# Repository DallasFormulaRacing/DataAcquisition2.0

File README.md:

> This repository was archived on Jan 10, 2025.

# `DataAcquisition2.0`

---
## Deprecation Notice 🚨
This repository has been deprecated. It is no longer actively maintained or updated. For the current and active IC Embedded project, please refer to the Wheel Base Sensor System [ repository](https://github.com/DallasFormulaRacing/WheelBaseSensorSystem).

---
🏁 For documentation, checkout our [Wiki](https://github.com/DallasFormulaRacing/DataAcquisition2.0/wiki)!

- Firmware libraries are maintained in the [DAQ Firmware Libraries](https://github.com/DallasFormulaRacing/DAQ-Firmware-Libraries) repo.
- Custom PCB revisions are maintained in the [DAQ-PCB](https://github.com/DallasFormulaRacing/DAQ-PCB) repo.
- When you clone this library, make sure that you add the --recurse-submodules flag
  
## Table of Contents
1. [Objective](#objective)
2. [User Features](#user-features)
3. [Hardware and Equipment](#hardware-and-equipment)
4. [Firmware Tech Stack](#firmware-tech-stack)
5. [Automation](#automation)
6. [Future Plans](#future-plans)
7. [Deprecated Technologies](#deprecated-technologies)

## Objective:
- A Data Acquisition (DAQ) System for interfacing with the vehicle ECU and additional sensors.
- Build the first fully-fledged DAQ with re-usable code through:
    - The Layered Architecture design pattern
    - Modularity of components
    - Hardware abstraction
- Efficiently record data to a CSV file for system testing & refinement of other vehicle components via analyses.
- Make sensor data conveniently accessible for the whole DFR organization.
- To be used in tandem with DFR's [DataAnalyzer](https://github.com/DallasFormulaRacing/DataAnalyzer).

## User Features
| Supported Logging Method | Library Completion    |
| :----------------------- | :--------------------:|
| Micro-SD Card            |                       |
| USB Flash Drive          | <span>&#10004;</span> |
| Wireless Transmission    |                       |

## Hardware and Equipment
### Target Device
The [STM32 Nucleo F429ZI](https://www.st.com/en/evaluation-tools/nucleo-f429zi.html) microcontroller development board is used as the current target device for code merged to the `main` and `develop` branches. Theoretically, other Arm Cortex M4 based STM32 devices with the necessary peripherals should be able to run the same program.

### Input
| Component Type        | Supported Hardware Device                                                                                            | Library Completion    |
| :-------------------- |:-------------------------------------------------------------------------------------------------------------------- | :--------------------:|
| Linear Potentiometer  | - [SLS 1322-3](https://www.activesensors.com/products/linear-position-sensors/general-purpose-linear-potentiometers) | <span>&#10004;</span> |
| Accelerometer         | - [LSM303DLHC](https://www.adafruit.com/product/1714)                                                                | <span>&#10004;</span> |
| Gyroscope             | - [L3GD20H](https://www.adafruit.com/product/1714)                                                                   | <span>&#10004;</span> |
| Magnetometer          | - [L3GD20H](https://www.adafruit.com/product/1714)                                                                   | <span>&#10004;</span> |
| GPS/GNSS              | - [NEO-M9N](https://www.sparkfun.com/products/15733)                                                                 |                       |
| Strain Gauges         |                                                                                                                      |                       |
| Tire Temperature      | - [MLX90614](https://www.sparkfun.com/products/9570)                                                                 |                       |
| ECU                   | - [PE3-8400P](https://pe-ltd.com/product/pe3-8400p/)                                                                 | <span>&#10004;</span> |

For additional information regarding each device and its implemention, refer to our [Wiki](https://github.com/DallasFormulaRacing/DataAcquisition2.0/wiki).

### Output
A CSV file with associate a timestamp with the following sampled data.

| Computed Output                | Supported Units                                         |
| :----------------------------- |:------------------------------------------------------- |
| Suspension Travel Displacement | - Inches <br /> - Millimeters                           |
| Acceleration (3 DoF)           | - m/s^2 <br /> - Gs                                     |
| Rotational Velocity (3 DoF)    | - Degrees per second <br /> - Radians per second        |
| Location Coordinates           | - Altitude <br /> - Latitude <br /> - Longitude         |
| External Force                 | - Stress <br /> - Torque <br /> - Pressure              |
| Tire Temperature               | - Farenheit <br /> - Celsius                            |
| Motor Shaft Speed              | - Revolutions per Minute (RPM)                          |
| Throttle Position              | - Percentage                                            |
| Fuel Open Time                 | - Milliseconds                                          |
| Ignition Angle                 | - Degrees                                               |
| Atmospheric Pressure           | - Pound per Square Inch (PSI) <br /> - Kilopascal (kPa) |
| Intake Manifold Pressure       | - Pound per Square Inch (PSI) <br /> - Kilopascal (kPa) |
| Exhaust Oxygen                 | - Lambda                                                |

## Firmware Tech Stack
- STM32 Hardware Abstraction Layer ([HAL](https://www.st.com/resource/en/user_manual/um1725-description-of-stm32f4-hal-and-lowlayer-drivers-stmicroelectronics.pdf))
  - Generated by STM32CubeMX within the CubeIDE environment, which also provides the `arm-none-eabi` toolchain.
  - Serves as a set of drivers or a Board Support Package (BSP) to interface with the microcontroller.
- [FreeRTOS](https://www.freertos.org/index.html)
  - Multi-threading and concurrent programming.
  - For optimizing timing and performance.
- [CMSIS-RTOS v2](https://www.keil.com/pack/doc/CMSIS/RTOS2/html/group__CMSIS__RTOS.html)
  - Not to be mistaken for another RTOS framework.
  - An abstraction layer for interacting with an RTOS framework (i.e., FreeRTOS).
- [FatFS](http://elm-chan.org/fsw/ff/)
  - For maintaining the FAT file system.
  - Allows users to access the resulting CSV file on any device

## Automation
- Unit tests are developed using [Google Test](https://google.github.io/googletest/) and are maintained in `DAQ_System/Tests`.
- See our [Unit Testing page](https://github.com/DallasFormulaRacing/DataAcquisition2.0/wiki/Unit-Testing) for running them locally by leveraging [Docker](https://docs.docker.com/get-started/overview/).
- Continuous Integration (CI)
  - The firmware is compiled as an stm32CubeIDE project using the following GitHub Action: [xanderhendriks/action-build-stm32cubeide](https://github.com/marketplace/actions/build-stm32cubeide-project).
  - The unit tests are compiled and ran using [CMake](https://cmake.org/cmake/help/latest/index.html) with [Ninja](https://ninja-build.org/manual.html). 

## Future Plans
- Developing for a dual-core STM32H7 microcontroller.
  - The Cortex M4 core may focus on sampling data from sensors.
  - The Cortex M7 core may focus on outputting the processed data.
  - Both cores may run FreeRTOS for organizational purposes.
  - Both cores may communicate and synchronize with each other using the OpenAMP framework.

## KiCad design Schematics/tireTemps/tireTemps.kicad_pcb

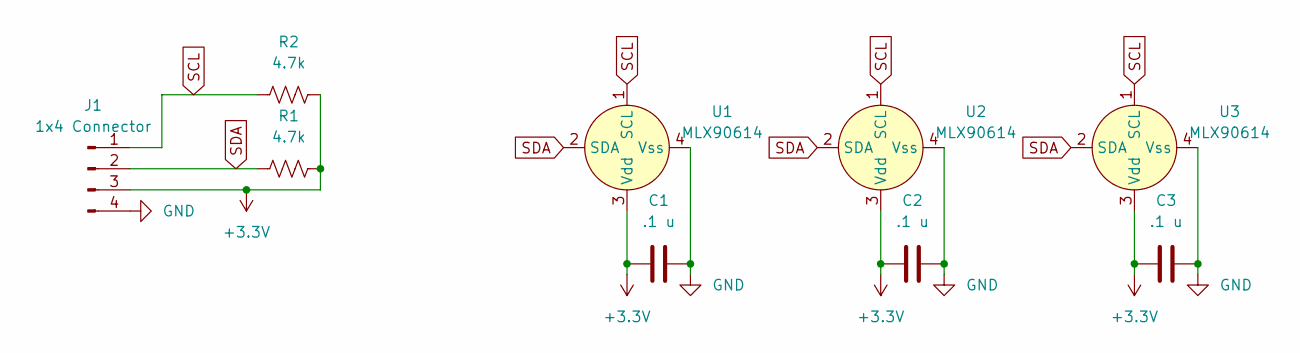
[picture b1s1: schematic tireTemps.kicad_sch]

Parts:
C1, C2, C3: .1 u; C_0603_1608Metric
J1: 1x4 Connector; Molex_KK-254_AE-6410-04A_1x04_P2.54mm_Vertical
R1, R2: 4.7k; R_0603_1608Metric
U1, U2, U3: MLX90614; TO-39-4

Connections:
+3.3V: C1.1, C2.1, C3.1, J1.3, R1.2, R2.2, U1.3 (Vdd), U2.3 (Vdd), U3.3 (Vdd)
GND: C1.2, C2.2, C3.2, J1.4, U1.4 (Vss), U2.4 (Vss), U3.4 (Vss)
SCL: J1.1, R2.1, U1.1 (SCL), U2.1 (SCL), U3.1 (SCL)
SDA: J1.2, R1.1, U1.2 (SDA), U2.2 (SDA), U3.2 (SDA)

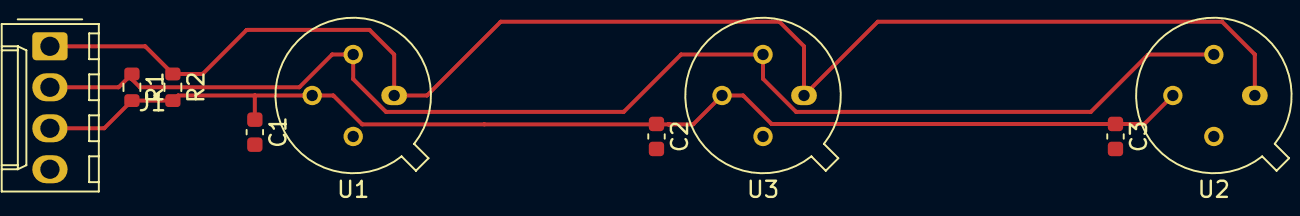
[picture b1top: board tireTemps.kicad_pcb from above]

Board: 2 copper layers, 9 parts (0 on the bottom side), 4 nets.

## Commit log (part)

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2022-10-04 changed potentiometer to use template class analogSensor
2022-10-05 simple class and header for potentiometer implmenting equation for linear potentiometers
2022-10-17 Bazel's LinPot code w/ modifications
2022-10-24 Getting valid temperature values
2022-10-28 Delete Arduino_Sub_DAQ
    I made a file instead of a folder.
2022-10-30 Update good_data.ino
    Added back in the third bit for the Prs variable
2022-11-01 final changes, style and heading
2022-11-02 Update and rename good_data.ino to air_pressure_code_v2.ino
    - Added sd card functionality
    - Removed unused variables
    - added functions for the transfer functions
    - fixed the switch issue
2022-11-02 Small style changes
2022-11-02 Update air_pressure_code_v2.ino
    Renamed P1 to I2C_ADDRESS
2022-11-07 1st response to PR comments
2022-11-07 Update air_pressure_code_v2.ino
    fixed formatting, variable names and array sizes.
2022-11-07 Removing minor spacing error
2022-11-10 changes made to work with board, added mbed_app.json, works with printf or cout natively to serial monitor
2022-11-17 Update air_pressure_code_v2.ino
    got rid of some variables, still working on incrementing file names for each flip of a switch.
2022-11-29 formatting changes
    added static global variables, changed name of variables and some general formatting
2022-12-16 Fixed sensor reading + quality of life changes: output formatting, renamed variables, removed unused library
2022-12-23 Modified names, added ComputeAverageTemperature()
2022-12-26 Acc/Mag Mbed library validation for raw values
2022-12-28 Updated minimal can interface for testing
2022-12-29 Added library, quick fixes for temp4
2023-01-01 New proj folder in QT 5.15, will attempt to build on its own on RPI 3 B+ arm64 to see compatability between arm64 and amd64 x86_64
2023-01-04 Added inheritence and polymorphism. Untested
2023-01-10 FATFileSystem class with SDBlockDevice demo
2023-01-11 Changed pressure multiplier to twenty, changed to start-average8 sensor command
2023-01-27 imported gyro interface library
2023-02-07 declared file_system and block_device in the main() local scope, initialized pos to 0 by default, created a mount() and unmount() functions for filesystem with error checking, created file_open(), fi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
2023-02-09 cleaned up old code and unnecessary comments
2023-02-10 added model number of potentiometer to potentiometer interface
2023-02-10 Moved constant from global scope to private, inside the namespace and class
2023-02-15 cleaned up the old implementation and finished style changes, going to move on and start working on a csv implementation
2023-02-16 Added main comments, removed commented mvp of linpots
2023-02-17 removed empty Adapters dir
2023-02-24 reorganizing the code
    I changed the opening curly brackets to be in line with the statements. I removed the if statement from the for loop of the AverageOffsetCalc() function. I added snake case for variables and pascal c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
2023-02-25 accel interface with calibration and conversion in sensor library
2023-02-28 replaced arbitrary sensors with the lin pots we have, got rid of error code, we will be using a separate log file for system error messages.
2023-03-01 decided to make buffer a member variable for data_logger
2023-03-01 renamed files to reflect that the data logging class is an SD implementation of the data logger interface as discussed in the task description
2023-03-06 Rename SDDataLogger.hpp to SdDataLogger.hpp
2023-03-06 just a couple minor fixes I forgot about
2023-03-10 data1.csv & data2.csv creation upon detection of pre-existing file with matching name
2023-03-10 reverted back to origin FileOpen(), added status and double file pointer, renaming logic moved to initialization in main()
2023-03-15 Uploaded linpot photos
2023-03-16 Added overarching auto reload timer to signal output writing
2023-03-17 consolidated the bridge, migrated to unique_ptr for efficiency and code size, connected to main
2023-04-01 Corrected typo in high level diagram, added svg alternative
2023-04-06 Added backup zipped schematics to gitignore
2023-04-09 renamed sampling variables to logging for transparency
2023-04-12 added todo comment
2023-04-13 Added output for mm and in
2023-04-14 unused variable
    got rid of unused variable
2023-04-21 added update from csv file writing branch that creates a new data file each time the reset button is pressed and adds a status return from the FileOpen function, still debugging the fatal runtime err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
2023-04-22 made changes from PR comments, since file_system_ is now initialized in the header file I got rid of the file system parameter in the mount and unmount functions
2023-04-23 Created a separate, local, write_buffer in main.cpp. main writes to that buffer and uses that as input for FileWrite(), which then copies that over to its own write_buffer_ and writes that to the fil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
2023-05-12 added button toggling, decoupled logging conditions
2023-05-13 initial draft of daq class. moved linpots to daq class
2023-05-13 added sd data logger to bridge
2023-05-14 replaced logging for loop with while loop
2023-06-15 adding code for the abstract interface
    added 6 files
    -L3GD20H.h
    -L3GD20H.cpp
    -igyroscope.hpp
    -gyroscope_l3gd20h.hpp
    -gyroscope_l3gd20h.cpp
2023-06-18 resolved conflicting main functions
2023-07-15 Resolved PR feedback comments
2023-07-15 Moved files
2023-08-20 Moved/renamed accelerometer drivers, & removed old gyro drivers
2023-08-22 made real acceleration & gravity factor internal to the class
2023-08-23 Moved & renamed methods
2023-08-23 Cleaned up main file
2023-08-25 Added sdio breakout board image
2023-09-13 Acceleromter/Gyroscope product image
2023-11-01 consolidated and archived Arduino programs
2023-11-01 Re-added mbed-os as a submodule for the deprecated Mbed_DAQ/
2023-11-13 added printf retargeting, enabled float numbers, brute-forced ADC readings in Task1 thread
2023-11-13 Added cubeIDE github action for CI
2023-11-15 Added quickstart unit test
2023-11-15 re-consolidated checkout into jobs
2023-11-15 cleaned up action.yaml
2023-11-16 updated action workflow with installing ninja
2023-11-17 removed testing script in favor of ninja commands, updated CI workflow
2023-11-20 re-aligned checkmark
2023-11-20 removed on pull_request event for CI build to remove duplicate builds on PRs
2023-11-26 moved app files into Src folder
2023-11-27 Created new Project directory due to conflicting nested CMakeLists
2023-12-09 Added front underscore to private adc
2023-12-15 Introducing cpp doc pages using doxygen, breathe, and sphinx within a docker container
2023-12-16 moved filter configs from main.c to app.cpp
2023-12-16 added missing comma
2023-12-22 multiple filters, parsing and decoding, and refactoring code
    This commit is comprised of three major parts
    1.) Multiple filters enabled
    2.) parsing function
    3.) Decoding function
    Multiple filters
    including multiple filters is rather straightforward. All you need to do is reinitialize the CAN filter structure but change the filter bank you are using. To do this is rather simple and I could hav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
2023-12-27 can interrupt flag bug fix
    Previously I forgot to reset the flag bit to 0 after each iteration. So at the end of the if statement that checks for the flag bit status, I reset the flag bit
2023-12-30 Declared ECU and CAN classes
2023-12-30 First draft of ECU CAN frames
2024-01-02 Corrected byte parsing overflow bug, updated names, added skeleton unit test cases
2024-01-03 renamed frame format to frame parsing, removed trivial unit tests
2024-01-05 Updated unit tests for updated type bit parsing
2024-01-14 Added more ECU sample data
2024-01-19 syntax fixes
    - removed any instance of magnetometer
    - added some variables for array sizes to reduce the number of "magic number" in the code
2024-01-20 Minimal draft of BxCan class
2024-01-24 temp
2024-01-25 Cleaned up bxcan_stmf4 class
2024-02-01 Added CAN ID subscribing and peripheral starting to ICan interface
2024-02-05 fixed some errors with with way OUT_X_L register is used
2024-02-05 removed the lsm6dsox gyro files since they aren't relevant to this PR
2024-02-07 changed register names on the .hpp and added comments for standard libraries, ST HAL dependencies, and DFR dependencies
2024-02-08 added the custom FSR and ODR functinos to the accelerometer
2024-02-08 added the FSR and ODR functions to the LSM6DSOX library for gyroscope
2024-02-08 PE3 ECU getter methods
2024-02-15 added standard Libraries,DFR Dependencies, and ST HAL comments where I forgot to add them. Added uint8_t data type to the eunmerations and added a new class SensorConfiguration to the enumerations. A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
2024-02-17 added the enumerations into the class scope of the LSM6DSOX
2024-02-23 Added POSIX compliant flags for opening files
2024-02-24 Fixed register bit placement of the ODR and FSR functions. Removed the linear regression equation from ComputeAcceleration() in favor of sensitivity factors, added a switch case to the setFSR() since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
2024-03-01 Modified FrameFormatX vector to be static and updated unit tests
2024-03-04 fixed FSR() and ODR()
2024-03-06 small changes to compile header
2024-03-07 added wrapper to accel class
2024-03-12 Converted CircularQueue to a template class, added unit tests
2024-03-12 Updated description for updating block device storage capacity counts
2024-03-14 changed header path
2024-03-24 moved dev add, changed sensor and app to fit
2024-03-27 First draft of data logger
2024-03-28 small change hopefully work
2024-03-31 changes to how recieve works
2024-04-02 capitalization
2024-04-02 Temporarily disabled RTOS
2024-04-10 nomenclature
2024-04-11 Abstracted the GPIO peripheral for the toggle switch
2024-04-11 Cleaned up dependencies to be in alphabetical order
2024-04-12 Added an abstracted mutex to the CircularQueue
2024-04-16 Integrated the CircularQueue into DataLogger
2024-04-18 RTOS timer
2024-04-18 Removed unused blocking code
2024-04-19 Recovered toggle switch GPIO
2024-04-19 Cleanup
2024-04-21 added enum class to FSR, ODR functions, kept the enum class in the concrete class, used shared pointer instead of a unique pointer, and used a namespace to scope the FSR and ODR enums.
2024-04-22 removed the namespaces for FSR and ODR and moved the enum into the class
2024-04-23 Added accelerometer and gyroscope to CSV
2024-04-24 combined the receive function into the ReadRaw()
2024-04-25 added transmit :3
2024-04-26 removed DisplacementInches() and DisplacementMillimeters() out of the initialziation since they are in the for loop()
2024-04-27 Added volatile keyword for variables updated within interrupt callbacks
2024-05-02 Restored hardware timer interrupt
2024-05-03 Enable submodules in CI build
2024-05-12 Updated #include lines
2024-05-12 removed unit test and api docs directories
2024-05-16 changing submodule
2024-05-16 matched cproject with develop, updated libs
2024-05-17 changed app to match new data logger
2024-05-22 update submodules
2024-06-06 submodule things
2024-06-07 test submodule in CI build
2024-06-07 changed submodule branch now without qoutes
2024-06-15 nart excplicitly disabled, debugging in app, relay thread
2024-07-02 minor restructuring in app, transmission works
2024-07-03 updated transmission code
2024-07-07 changed nomenclature and added write only can bus
2024-07-12 testing transmission with linpot hooked up
2024-07-31 missed some testing changes, TODO: move relay to own queue
2024-08-05 1Mhz CAN buad rate
2024-08-21 rx pin pull up
2024-08-26 switched back to 0.5hz
2024-09-20 arb ids
2024-09-27 rx pullup enabled, 100hz
2024-10-12 autocross, removed printf
2024-10-12 retargeting code
2024-10-13 working printf
